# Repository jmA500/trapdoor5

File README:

This repository contains all the files to construct a Trapddor
expansion for the Amiga 500. There are some variants available. For
more information see the project website:

     https://www.jm27.de/for-commodore-amiga-500-1-8-mb-2mb-trapdoor-memory-expansion/

One variant uses a universal GARY Adapter (T3), the second one a
spcialized GARY adapter (T4). The T3 variant has as a main benefit
that the GARY adapter can be used with other original memory expansion
boards using a 74'139 to multiplex the CAS lines. The T4 version's
main feature is that there is no exra connection needed between the
GARY adapter and the Trapdoor board. 

Directories:

- doc: some documentation, needs to be extended

- pcb-trapdoor: kicad files for the pcb for the trapdoor assembly,
  both variants
- gal-trapdoor: Source and JED files for the GAL used on the trapdoor board
  CBR5SEL is needed for the T3 variant of the GARY adapter,
  CBR5EX is for the T4 variant
-pcb-gary-sel: the T3 GARY adater, kicad files
-pcb-gary-ext: the T4 GARY adapter, kicad files

- gal-gary: the corresponding GAL files
  GARY-T3: for the T3 variant
  GARY-T4: for the T4 variant

The PLD files can be compiled with WinCUPL available from Microchip. I
would be grateful fo a suggestion of a free alternative.

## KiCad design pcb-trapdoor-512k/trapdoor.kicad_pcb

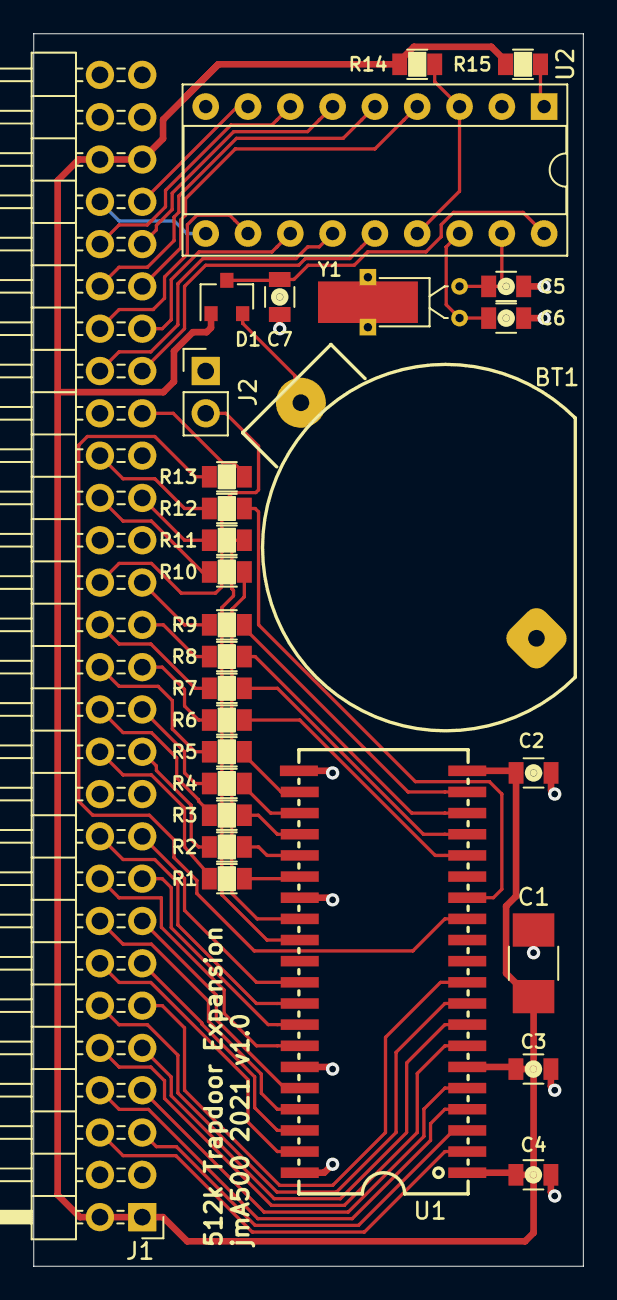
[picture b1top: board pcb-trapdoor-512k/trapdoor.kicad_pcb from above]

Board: 2 copper layers, 33.0 x 74.0 mm, 29 parts (0 on the bottom side), 61 nets.

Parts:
BT1: CR2032 Battery Holder; BAT-CR2023-45
C1: 22µ; C_1210_HandSoldering
C2, C3, C4: 100n; C_0805
C5, C6: 22p; C_0805
C7: 1µ; C_0805
D1: BAT54C; SOT-23
J1: TRAPDOOR-CONNECTOR; Pin_Header_Angled_2x28_Pitch2.54mm
J2: CONN_01X02; Pin_Header_Straight_1x02_Pitch2.54mm
R1, R2, R3, R4, R5, R6, R7, R8, R9, R10, R11, R12, R13: 68R; R_0805
R14, R15: 4k7; R_0805
U1: DRAM-256kx16-SOJ; SOJ-40
U2: MSM6242; DIP-18_W7.62mm_Socket
Y1: 32,768kHz; Crystal_DS26_d2.0mm_l6.0mm_Horizontal_1EP_style2

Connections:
+5V: C1.1, C2.2, C3.2, C4.2, D1.1, J1.1, J1.2, J1.51, J1.52, R14.2, R15.1, U1.1, U1.6, U1.20
/A0: R2.1, U1.25
/A1: R1.1, U1.26
/A2: R4.1, U1.23
/A3: R3.1, U1.24
/A4: R6.1, U1.16
/A5: R5.1, U1.22
/A6: R8.1, U1.18
/A7: R7.1, U1.17
/A8: R9.1, U1.19
/D0: J1.5, U1.3
/D1: J1.6, U1.2
/D2: J1.7, U1.5
/D3: J1.8, U1.4
/D4: J1.9, U1.8
/D5: J1.10, U1.7
/D6: J1.11, U1.10
/D7: J1.12, U1.9
/D8: J1.13, U1.38
/D9: J1.14, U1.39
/D10: J1.15, U1.36
/D11: J1.16, U1.37
/D12: J1.17, U1.33
/D13: J1.18, U1.34
/D14: J1.19, U1.31
/D15: J1.20, U1.32
/R~W: R13.1, U1.13
/XA2: J1.45, U2.4
/XA3: J1.46, U2.5
/XA4: J1.47, U2.6
/XA5: J1.48, U2.7
/XD0: J1.41, U2.14
/XD1: J1.42, U2.13
/XD2: J1.43, U2.12
/XD3: J1.44, U2.11
/~CASL: R11.1, U1.29
/~CASU: R10.1, U1.28
/~EXRAM: J1.32, J2.2
/~RAS: R12.1, U1.14
/~XCLKRD: J1.49, U2.8
/~XCLKWR: J1.50, U2.10
GND: BT1.2, C1.2, C2.1, C3.1, C4.1, C5.1, C6.1, C7.1, J1.3, J1.4, J1.21, J1.22, J1.33, J1.34, J1.53, J1.54, J2.1, U1.21, U1.27, U1.35, U1.40, U2.2, U2.9, Y1.3
unnamed: BT1.1, D1.2
unnamed: C5.2, U2.17, Y1.1
unnamed: C6.2, U2.16, Y1.2
unnamed: C7.2, D1.3, U2.18
unnamed: J1.23, R2.2
unnamed: J1.24, R1.2
unnamed: J1.25, R4.2
unnamed: J1.26, R3.2
unnamed: J1.27, R6.2
unnamed: J1.28, R5.2
unnamed: J1.29, R8.2
unnamed: J1.30, R7.2
unnamed: J1.31, R9.2
unnamed: J1.35, R11.2
unnamed: J1.36, R10.2
unnamed: J1.38, R12.2
unnamed: J1.39, R13.2
unnamed: R14.1, U2.3, U2.15
unnamed: R15.2, U2.1

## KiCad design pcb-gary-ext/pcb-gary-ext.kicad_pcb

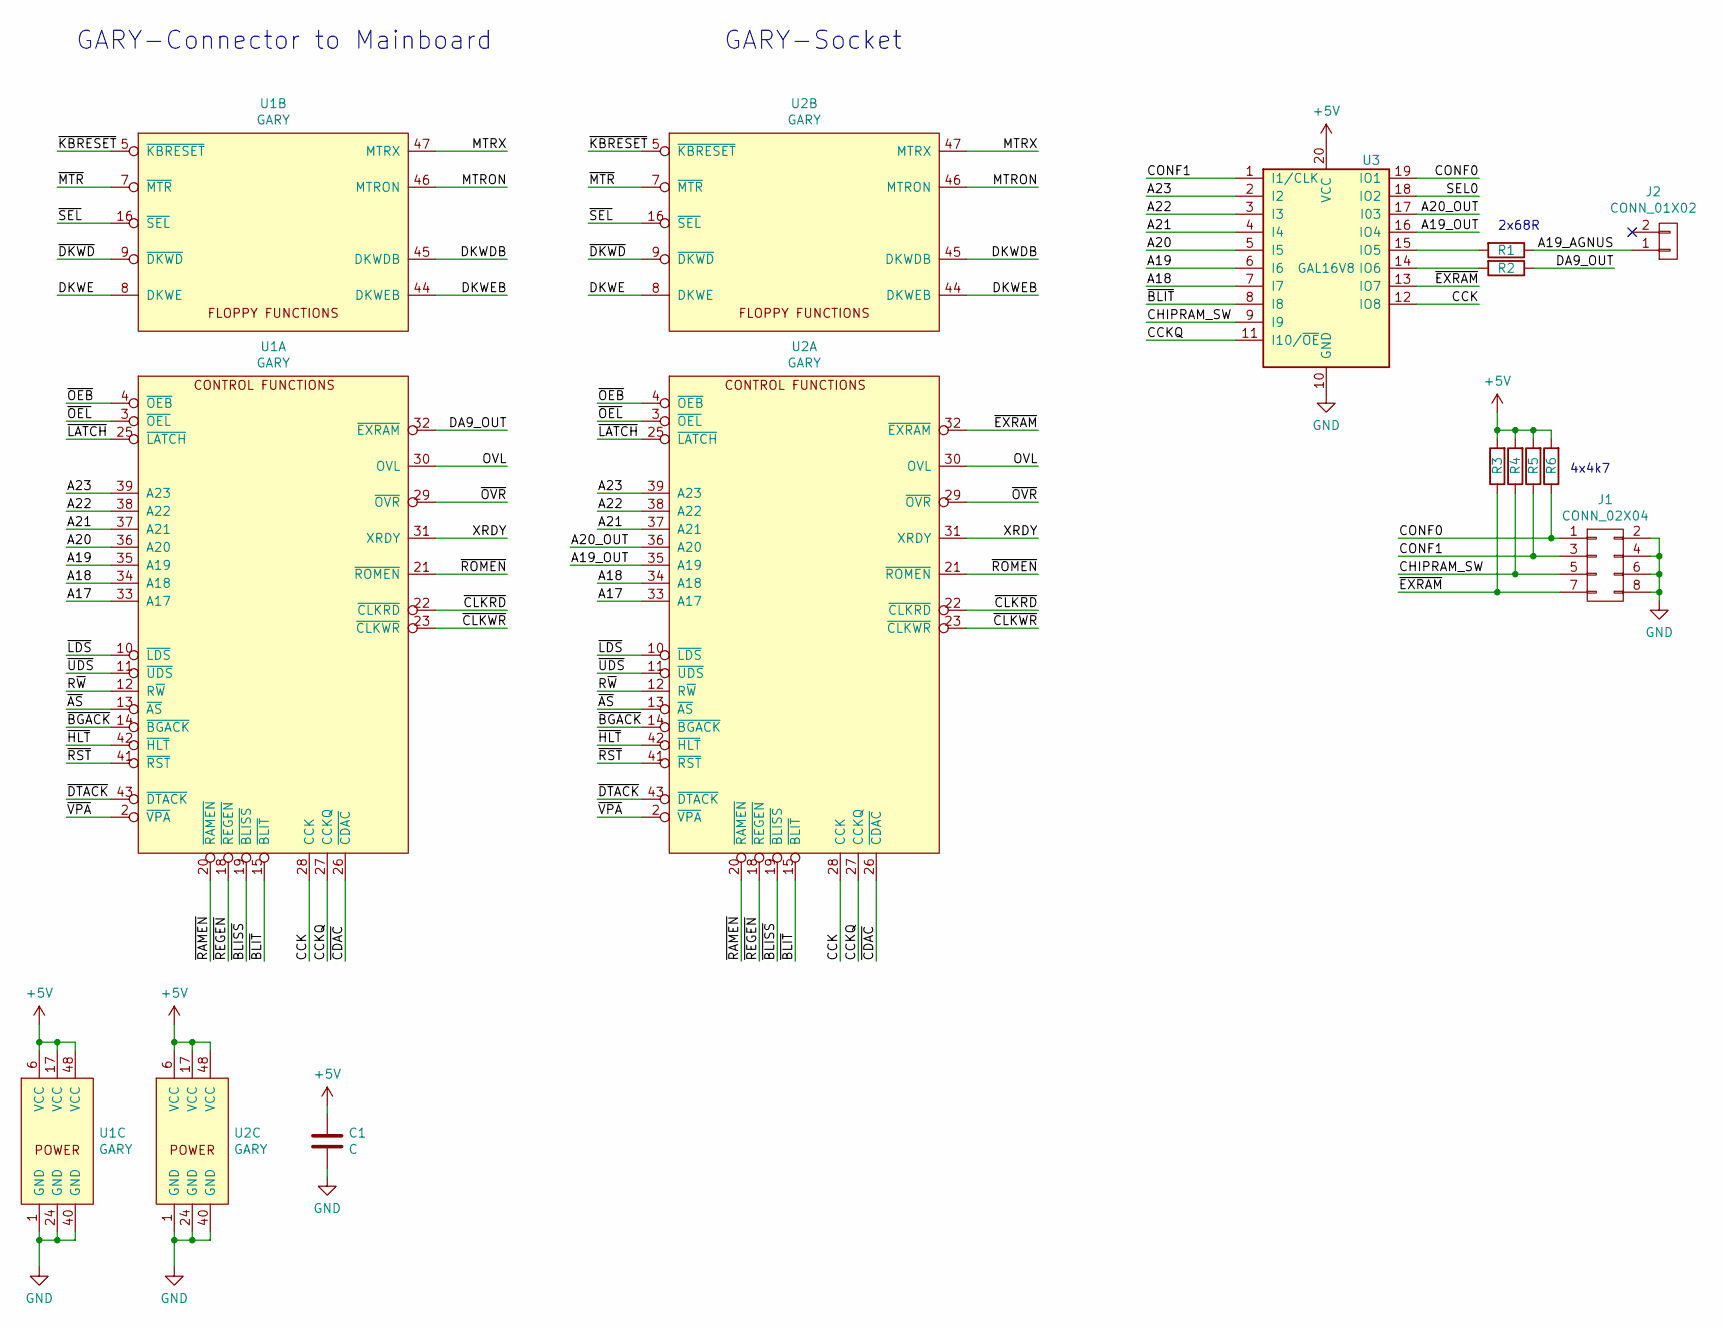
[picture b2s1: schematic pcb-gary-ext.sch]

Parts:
C1: C; C_0805
J1: CONN_02X04; Pin_Header_Straight_2x04_Pitch2.54mm
J2: CONN_01X02; MOLEX-KK-Angled-2
R1, R2: 68R; R_0805
R3, R4, R5, R6: 4k7; R_0805
U1, U2: GARY
U3: GAL16V8; DIP-20_W7.62mm

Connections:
+5V: C1.1, R3.2, R4.2, R5.2, R6.2, U1.6 (VCC), U1.17 (VCC), U1.48 (VCC), U2.6 (VCC), U2.17 (VCC), U2.48 (VCC), U3.20 (VCC)
/A17: U1.33 (A17), U2.33 (A17)
/A18: U1.34 (A18), U2.34 (A18), U3.7 (I7)
/A19: U1.35 (A19), U3.6 (I6)
/A19_AGNUS: J2.1, R1.1
/A19_OUT: U2.35 (A19), U3.16 (IO4)
/A20: U1.36 (A20), U3.5 (I5)
/A20_OUT: U2.36 (A20), U3.17 (I03)
/A21: U1.37 (A21), U2.37 (A21), U3.4 (I4)
/A22: U1.38 (A22), U2.38 (A22), U3.3 (I3)
/A23: U1.39 (A23), U2.39 (A23), U3.2 (I2)
/CCK: U1.28 (CCK), U2.28 (CCK), U3.12 (IO8)
/CCKQ: U1.27 (CCKQ), U2.27 (CCKQ), U3.11 (I10/~OE~)
/CHIPRAM_SW: J1.5, R4.1, U3.9 (I9)
/CONF0: J1.1, R6.1, U3.19 (IO1)
/CONF1: J1.3, R5.1, U3.1 (I1/CLK)
/DA9_OUT: R2.1, U1.32 (~EXRAM)
/DKWDB: U1.45 (DKWDB), U2.45 (DKWDB)
/DKWE: U1.8 (DKWE), U2.8 (DKWE)
/DKWEB: U1.44 (DKWEB), U2.44 (DKWEB)
/MTRON: U1.46 (MTRON), U2.46 (MTRON)
/MTRX: U1.47 (MTRX), U2.47 (MTRX)
/OVL: U1.30 (OVL), U2.30 (OVL)
/R~W: U1.12 (R~W), U2.12 (R~W)
/XRDY: U1.31 (XRDY), U2.31 (XRDY)
/~AS: U1.13 (~AS), U2.13 (~AS)
/~BGACK: U1.14 (~BGACK), U2.14 (~BGACK)
/~BLISS: U1.19 (~BLISS), U2.19 (~BLISS)
/~BLIT: U1.15 (~BLIT), U2.15 (~BLIT), U3.8 (I8)
/~CDAC: U1.26 (~CDAC), U2.26 (~CDAC)
/~CLKRD: U1.22 (~CLKRD), U2.22 (~CLKRD)
/~CLKWR: U1.23 (~CLKWR), U2.23 (~CLKWR)
/~DKWD: U1.9 (~DKWD), U2.9 (~DKWD)
/~DTACK: U1.43 (~DTACK), U2.43 (~DTACK)
/~EXRAM: J1.7, R3.1, U2.32 (~EXRAM), U3.13 (IO7)
/~HLT: U1.42 (~HLT), U2.42 (~HLT)
/~KBRESET: U1.5 (~KBRESET), U2.5 (~KBRESET)
/~LATCH: U1.25 (~LATCH), U2.25 (~LATCH)
/~LDS: U1.10 (~LDS), U2.10 (~LDS)
/~MTR: U1.7 (~MTR), U2.7 (~MTR)
/~OEB: U1.4 (~OEB), U2.4 (~OEB)
/~OEL: U1.3 (~OEL), U2.3 (~OEL)
/~OVR: U1.29 (~OVR), U2.29 (~OVR)
/~RAMEN: U1.20 (~RAMEN), U2.20 (~RAMEN)
/~REGEN: U1.18 (~REGEN), U2.18 (~REGEN)
/~ROMEN: U1.21 (~ROMEN), U2.21 (~ROMEN)
/~RST: U1.41 (~RST), U2.41 (~RST)
/~SEL: U1.16 (~SEL), U2.16 (~SEL)
/~UDS: U1.11 (~UDS), U2.11 (~UDS)
/~VPA: U1.2 (~VPA), U2.2 (~VPA)
GND: C1.2, J1.2, J1.4, J1.6, J1.8, U1.1 (GND), U1.24 (GND), U1.40 (GND), U2.1 (GND), U2.24 (GND), U2.40 (GND), U3.10 (GND)
unnamed: R1.2, U3.15 (IO5)
unnamed: R2.2, U3.14 (IO6)

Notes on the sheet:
GARY-Connector to Mainboard
GARY-Socket
2x68R
4x4k7

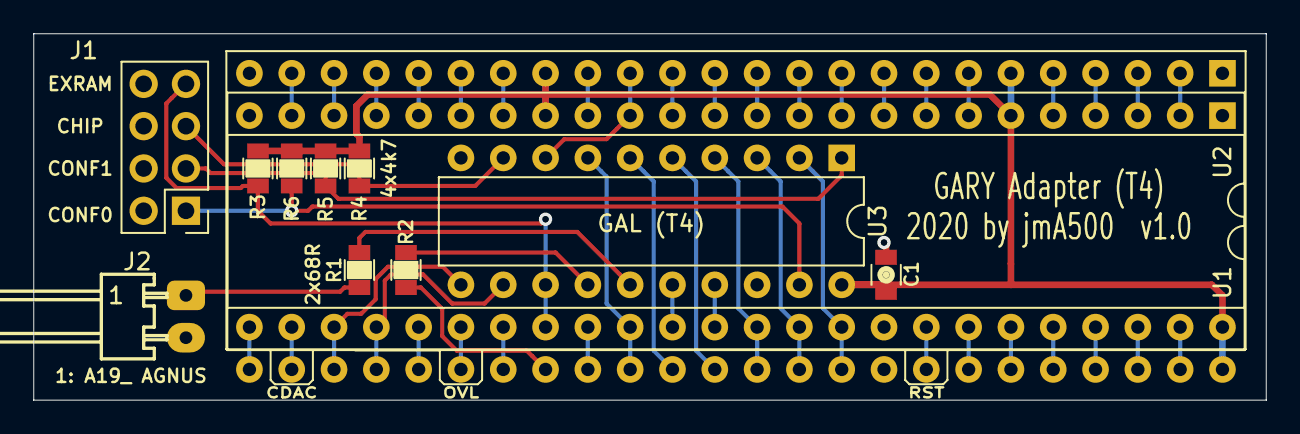
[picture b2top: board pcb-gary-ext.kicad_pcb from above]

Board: 2 copper layers, 74.0 x 22.0 mm, 12 parts (0 on the bottom side), 53 nets.

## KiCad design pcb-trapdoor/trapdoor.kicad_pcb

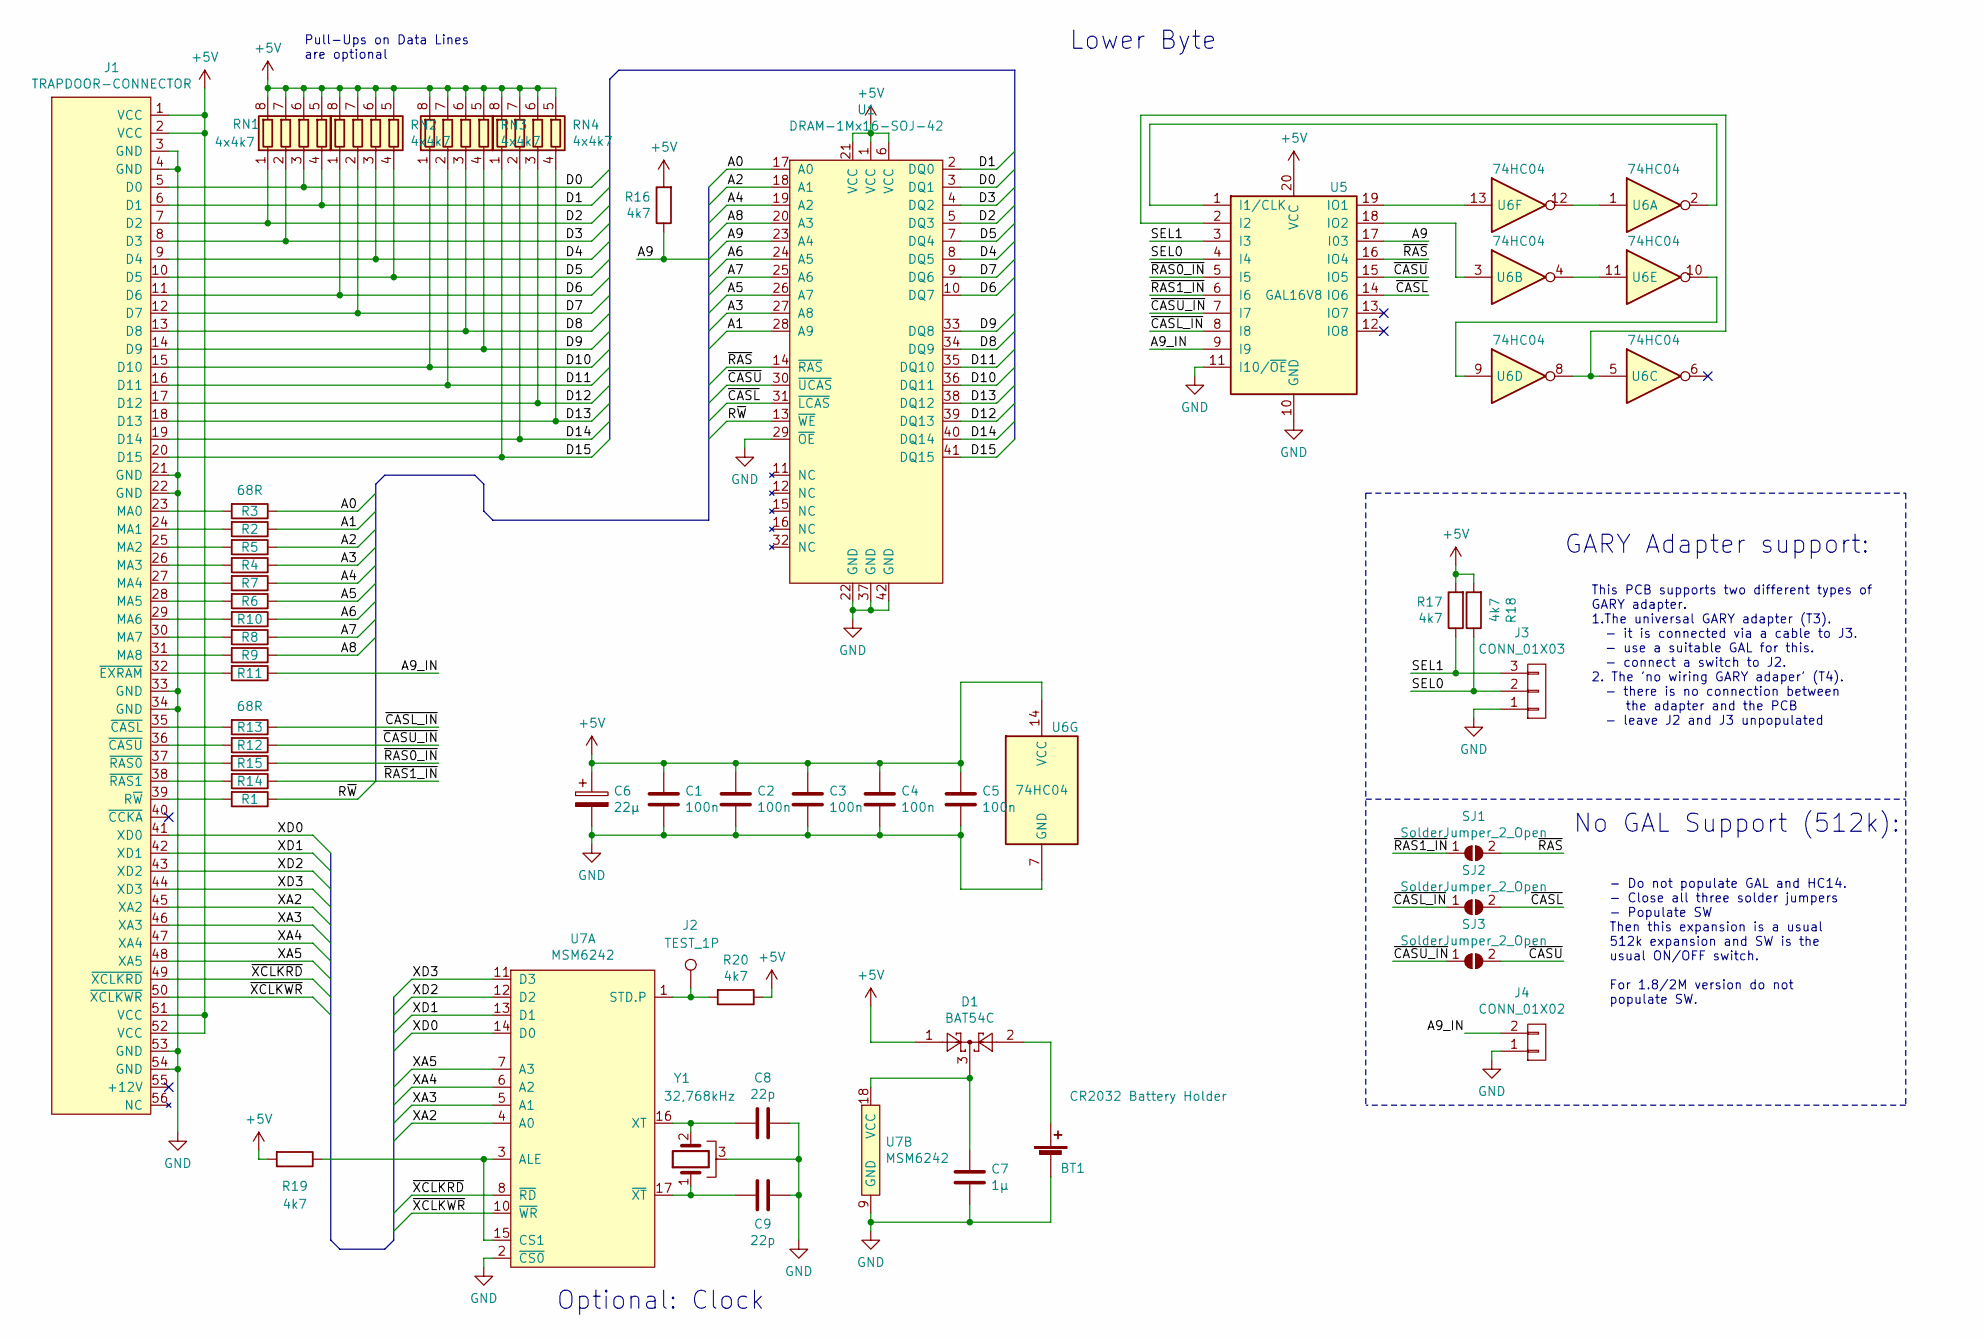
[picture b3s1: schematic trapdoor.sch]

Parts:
BT1: CR2032 Battery Holder; BAT-CR2032
C1, C2, C3, C4, C5: 100n; C_0805
C6: 22µ; C_1210_HandSoldering
C7: 1µ; C_0805
C8, C9: 22p; C_0805
D1: BAT54C; SOT-23
J1: TRAPDOOR-CONNECTOR; Pin_Header_Angled_2x28_Pitch2.54mm
J2: TEST_1P; Measurement_Point_Round-SMD-Pad_Small
J3: CONN_01X03; Molex_KK-6410-03_03x2.54mm_Straight
J4: CONN_01X02; Molex_KK-6410-02_02x2.54mm_Straight
R1, R2, R3, R4, R5, R6, R7, R8, R9, R10, R11, R12, R13, R14, R15: 68R; R_0805
R16, R17, R18, R19, R20: 4k7; R_0805
RN1, RN2, RN3, RN4: 4x4k7; R_Array_4x0603
SJ1, SJ2, SJ3: SolderJumper_2_Open; SMD-Jumper
U1: DRAM-1Mx16-SOJ-42; SOJ-42
U5: GAL16V8; PLCC-20_SMD-Socket
U6: 74HC04; SOIC-14_3.9x8.7mm_Pitch1.27mm
U7: MSM6242; DIP-18_W7.62mm_Socket
Y1: 32,768kHz; Crystal_DS26_d2.0mm_l6.0mm_Horizontal_1EP_style2

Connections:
+5V: C1.2, C2.2, C3.2, C4.2, C5.2, C6.1, D1.1, J1.1 (VCC), J1.2 (VCC), J1.51 (VCC), J1.52 (VCC), R16.2, R17.2, R18.2, R19.2, R20.1, RN1.5 (R4.2), RN1.6 (R3.2), RN1.7 (R2.2), RN1.8 (R1.2), RN2.5 (R4.2), RN2.6 (R3.2), RN2.7 (R2.2), RN2.8 (R1.2), RN3.5 (R4.2), RN3.6 (R3.2), RN3.7 (R2.2), RN3.8 (R1.2), RN4.5 (R4.2), RN4.6 (R3.2), RN4.7 (R2.2), RN4.8 (R1.2), U1.1 (VCC), U1.6 (VCC), U1.21 (VCC), U5.20 (VCC), U6.14 (VCC)
/A0: R3.1, U1.17 (A0)
/A1: R2.1, U1.28 (A9)
/A2: R5.1, U1.18 (A1)
/A3: R4.1, U1.27 (A8)
/A4: R7.1, U1.19 (A2)
/A5: R6.1, U1.26 (A7)
/A6: R10.1, U1.24 (A5)
/A7: R8.1, U1.25 (A6)
/A8: R9.1, U1.20 (A3)
/A9: R16.1, U1.23 (A4), U5.17 (I03)
/A9_IN: J4.2, R11.1, U5.9 (I9)
/D0: J1.5 (D0), RN1.3 (R3.1), U1.3 (DQ1)
/D1: J1.6 (D1), RN1.4 (R4.1), U1.2 (DQ0)
/D2: J1.7 (D2), RN1.1 (R1.1), U1.5 (DQ3)
/D3: J1.8 (D3), RN1.2 (R2.1), U1.4 (DQ2)
/D4: J1.9 (D4), RN2.3 (R3.1), U1.8 (DQ5)
/D5: J1.10 (D5), RN2.4 (R4.1), U1.7 (DQ4)
/D6: J1.11 (D6), RN2.1 (R1.1), U1.10 (DQ7)
/D7: J1.12 (D7), RN2.2 (R2.1), U1.9 (DQ6)
/D8: J1.13 (D8), RN3.3 (R3.1), U1.34 (DQ9)
/D9: J1.14 (D9), RN3.4 (R4.1), U1.33 (DQ8)
/D10: J1.15 (D10), RN3.1 (R1.1), U1.36 (DQ11)
/D11: J1.16 (D11), RN3.2 (R2.1), U1.35 (DQ10)
/D12: J1.17 (D12), RN4.3 (R3.1), U1.39 (DQ13)
/D13: J1.18 (D13), RN4.4 (R4.1), U1.38 (DQ12)
/D14: J1.19 (D14), RN4.2 (R2.1), U1.40 (DQ14)
/D15: J1.20 (D15), RN4.1 (R1.1), U1.41 (DQ15)
/R~W: R1.1, U1.13 (~WE)
/SEL0: J3.2, R18.1, U5.4 (I4)
/SEL1: J3.3, R17.1, U5.3 (I3)
/XA2: J1.45 (XA2), U7.4 (A0)
/XA3: J1.46 (XA3), U7.5 (A1)
/XA4: J1.47 (XA4), U7.6 (A2)
/XA5: J1.48 (XA5), U7.7 (A3)
/XD0: J1.41 (XD0), U7.14 (D0)
/XD1: J1.42 (XD1), U7.13 (D1)
/XD2: J1.43 (XD2), U7.12 (D2)
/XD3: J1.44 (XD3), U7.11 (D3)
/~CASL: SJ2.2 (B), U1.31 (~LCAS), U5.14 (IO6)
/~CASL_IN: R13.1, SJ2.1 (A), U5.8 (I8)
/~CASU: SJ3.2 (B), U1.30 (~UCAS), U5.15 (IO5)
/~CASU_IN: R12.1, SJ3.1 (A), U5.7 (I7)
/~RAS: SJ1.2 (B), U1.14 (~RAS), U5.16 (IO4)
/~RAS0_IN: R15.1, U5.5 (I5)
/~RAS1_IN: R14.1, SJ1.1 (A), U5.6 (I6)
/~XCLKRD: J1.49 (~XCLKRD), U7.8 (~RD)
/~XCLKWR: J1.50 (~XCLKWR), U7.10 (~WR)
GND: BT1.2 (-), C1.1, C2.1, C3.1, C4.1, C5.1, C6.2, C7.1, C8.1, C9.1, J1.3 (GND), J1.4 (GND), J1.21 (GND), J1.22 (GND), J1.33 (GND), J1.34 (GND), J1.53 (GND), J1.54 (GND), J3.1, J4.1, U1.22 (GND), U1.29 (~OE), U1.37 (GND), U1.42 (GND), U5.10 (GND), U5.11 (I10/~OE~), U6.7 (GND), U7.2 (~CS0), U7.9 (GND), Y1.3
unnamed: BT1.1 (+), D1.2
unnamed: C7.2, D1.3, U7.18 (VCC)
unnamed: C8.2, U7.16 (XT), Y1.2
unnamed: C9.2, U7.17 (~XT), Y1.1
unnamed: J1.23 (MA0), R3.2
unnamed: J1.24 (MA1), R2.2
unnamed: J1.25 (MA2), R5.2
unnamed: J1.26 (MA3), R4.2
unnamed: J1.27 (MA4), R7.2
unnamed: J1.28 (MA5), R6.2
unnamed: J1.29 (MA6), R10.2
unnamed: J1.30 (MA7), R8.2
unnamed: J1.31 (MA8), R9.2
unnamed: J1.32 (~EXRAM), R11.2
unnamed: J1.35 (~CASL), R13.2
unnamed: J1.36 (~CASU), R12.2
unnamed: J1.37 (~RAS0), R15.2
unnamed: J1.38 (~RAS1), R14.2
unnamed: J1.39 (R~W), R1.2
unnamed: J2.1, R20.2, U7.1 (STD.P)
unnamed: R19.1, U7.3 (ALE), U7.15 (CS1)
unnamed: U5.1 (I1/CLK), U6.2
unnamed: U5.2 (I2), U6.5, U6.8
unnamed: U5.18 (IO2), U6.3
unnamed: U5.19 (IO1), U6.13
unnamed: U6.1, U6.12
unnamed: U6.9, U6.10
unnamed: U6.4, U6.11

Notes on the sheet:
Optional: Clock
Lower Byte
Pull-Ups on Data Lines are optional
No GAL Support (512k):
- Do not populate GAL and HC14. - Close all three solder jumpers - Populate SW Then this expansion is a usual 512k expansion and SW is the usual ON/OFF switch. For 1.8/2M version do not populate SW.
GARY Adapter support:
This PCB supports two different types of GARY adapter. 1.The universal GARY adapter (T3). - it is connected via a cable to J3. - use a suitable GAL for this. - connect a switch to J2. 2. The 'no wiring GARY adaper' (T4). - there is no connection between the adapter and the PCB - leave J2 and J3 unp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

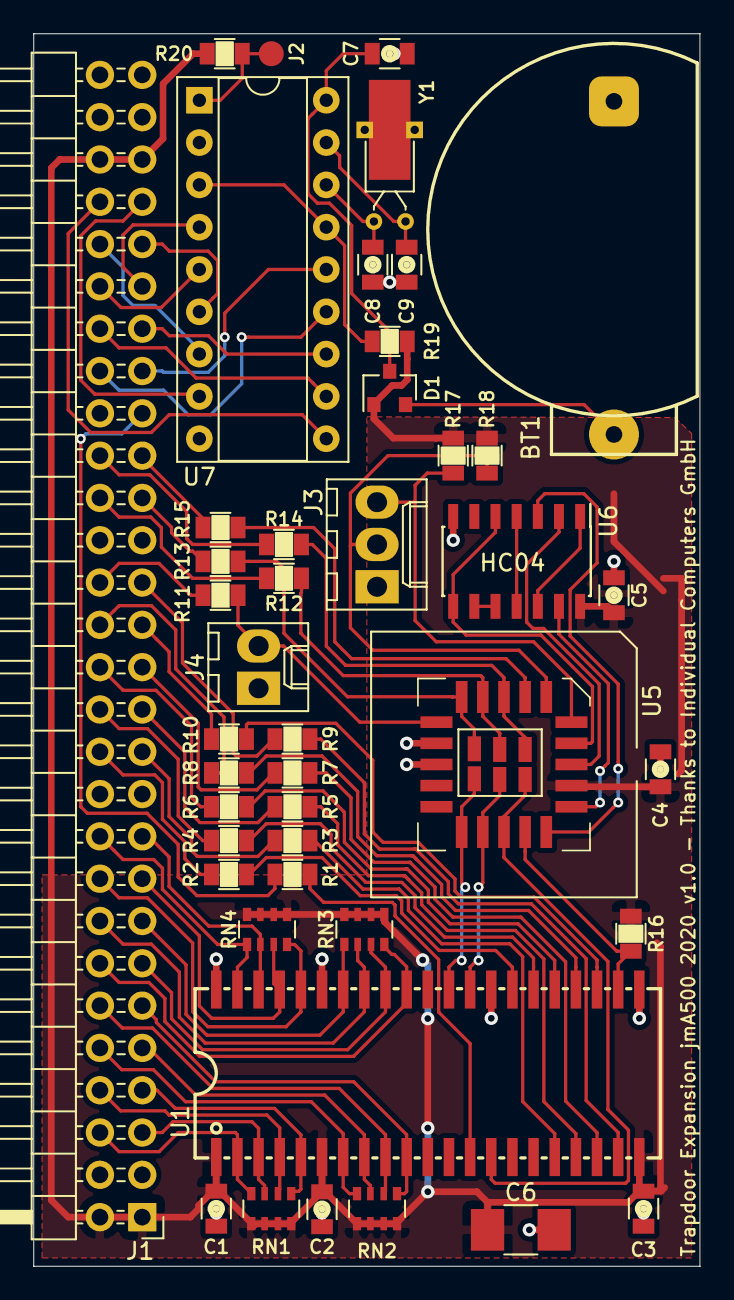
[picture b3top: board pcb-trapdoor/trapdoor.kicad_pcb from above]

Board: 2 copper layers, 40.0 x 74.0 mm, 47 parts (0 on the bottom side), 77 nets.

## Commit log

2020-03-05 Trapdoor Platine fertig. Platine kann für beide Gary-Adapter konfiguriert werden. Dazu CPLD-Code für beide Versionen.
2020-03-06 PCBs hinzugefügt.
2020-03-10 Update PCB für Trapdoor.
2020-03-22 Updated schmatic.
2020-03-22 README added
2020-03-22 Update Projektverzeichnis
2021-03-14 * Added PCB for 512k-Trapdoor expansion * Some repository cleanup
